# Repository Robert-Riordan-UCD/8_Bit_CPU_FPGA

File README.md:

# 8 Bit FPGA CPU

This is an 8-bit CPU design running on a Tang Nano 9k FPGA. The CPU design is based on [Ben Eaters Breadboard CPU](https://eater.net/8bit), which is based on the [Simple As Possible Computer](https://en.wikipedia.org/wiki/Simple-As-Possible_computer).

The CPU is made of 11 modules, which are designed in SystemVerilog and verified using [pyuvm](https://github.com/pyuvm/pyuvm).

This is a gif of the CPU calculating the fibonacci sequence and displaying it (in hexadecimal).

# Getting Started

This project is not fully complete yet and is currently only tested on my personal laptop and raspberry pi. However, this is the current process. (I am developing on Ubuntu 24 and used [this](https://www.geeklan.co.uk/?p=2919) guide to get up and running using an open source toolchain)

## Installation and Setup

The following programs are required:
1. ```yosys``` for synthisis.
2. ```nextpnr``` for place and route, and bitstream generation.
3. ```openFPGALoader``` for loading the bitstream.

```sudo apt insatll yosys nextpnr-gowin openfpgaloader```

Clone and navigate to the repository

```
git clone https://github.com/Robert-Riordan-UCD/8_Bit_CPU_FPGA
cd ./8_Bit_CPU_FPGA/
```

## Running

```make all upload```

## Testing

```pyuvm``` is required for testing.

```sudo apt install pyuvm```

To test each module navigate to the verif directory for that module and run make.

```
cd ./verif/<module>/
make
```

# Current Design Status

| Module                  | RTL | Verified | Runs on FPGA |
| :---------------------- | :-: | :-: | :-: |
| Clock                   |✅|✅|✅|
| Program Counter         |✅|✅|✅|
| A register              |✅|✅|✅|
| B Register              |✅|✅|✅|
| Memory Address Register |✅|✅|✅|
| Instruction Register    |✅|✅|✅|
| Random Access Memory    |✅|✅|✅|
| Arithmetic Logic Unit   |✅|✅|✅|
| Control                 |✅|✅|✅|
| Output                  |✅|✅|✅|
| Bus                     |✅|✅|✅|
| Bootloader              |✅|✅|✅|
||||
| Top                     |✅|❌|✅|

The output is currently in hexadecimal, because there was not enough LUTs on the Tang Nano 9k to implement a naive approach to decimal conversion using division. I will hopefully update this to a better approach soon.

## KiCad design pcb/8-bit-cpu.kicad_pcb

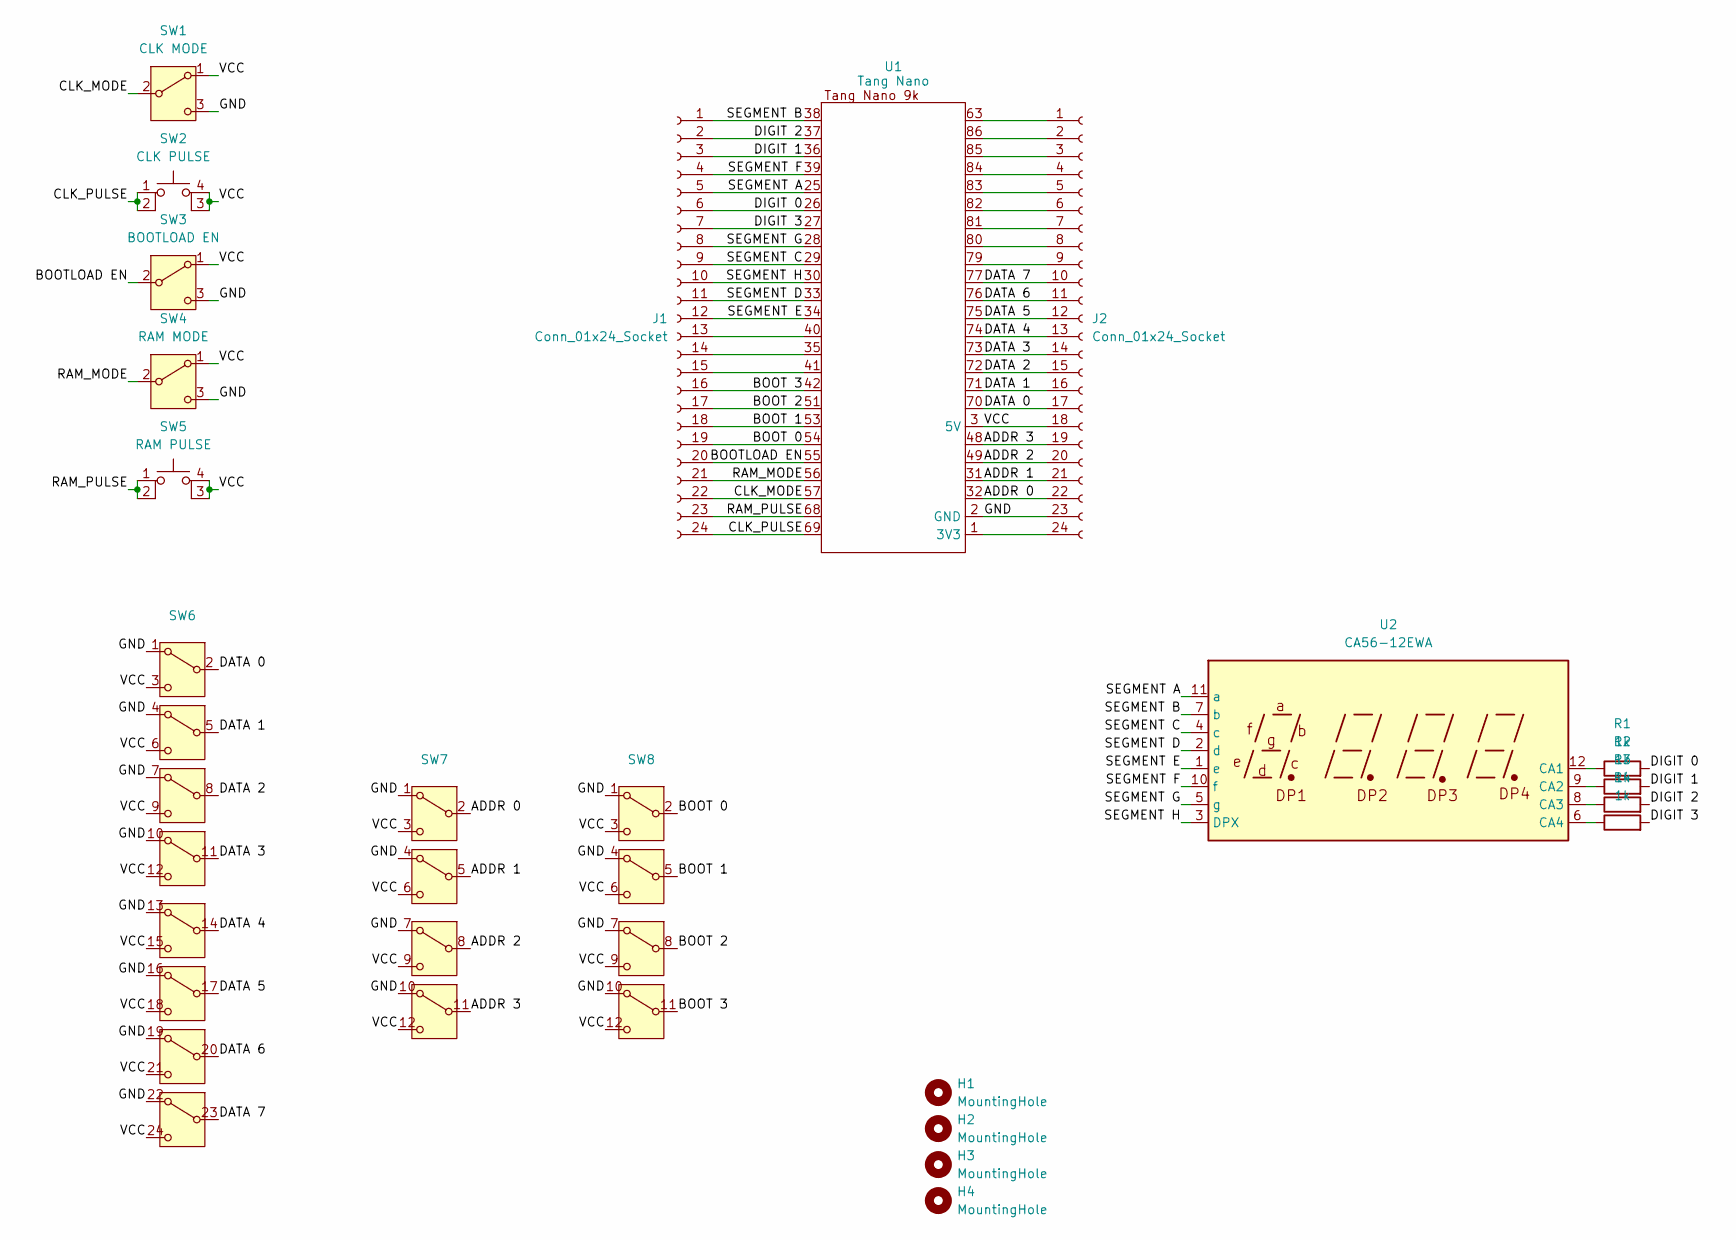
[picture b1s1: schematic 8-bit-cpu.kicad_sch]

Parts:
H1, H2, H3, H4: MountingHole; MountingHole_3.2mm_M3
J1, J2: Conn_01x24_Socket; PinHeader_1x24_P2.54mm_Vertical
R1, R2, R3, R4: 1k; R_Axial_DIN0309_L9.0mm_D3.2mm_P12.70mm_Horizontal
SW1: CLK MODE; DoubleThrowSwitch
SW2: CLK PULSE; tactile_switch
SW3: BOOTLOAD EN; DoubleThrowSwitch
SW4: RAM MODE; DoubleThrowSwitch
SW5: RAM PULSE; tactile_switch
SW6: 8xDoubleThrowSwitch
SW7, SW8: 4xDoubleThrowSwitch
U1: Tang Nano; TangNano
U2: CA56-12EWA

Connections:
/ADDR 0: J2.22, SW7.2, U1.32
/ADDR 1: J2.21, SW7.5, U1.31
/ADDR 2: J2.20, SW7.8, U1.49
/ADDR 3: J2.19, SW7.11, U1.48
/BOOT 0: J1.19, SW8.2, U1.54
/BOOT 1: J1.18, SW8.5, U1.53
/BOOT 2: J1.17, SW8.8, U1.51
/BOOT 3: J1.16, SW8.11, U1.42
/BOOTLOAD EN: J1.20, SW3.2 (B), U1.55
/CLK_MODE: J1.22, SW1.2 (B), U1.57
/CLK_PULSE: J1.24, SW2.1, SW2.2, U1.69
/DATA 0: J2.17, SW6.2, U1.70
/DATA 1: J2.16, SW6.5, U1.71
/DATA 2: J2.15, SW6.8, U1.72
/DATA 3: J2.14, SW6.11, U1.73
/DATA 4: J2.13, SW6.14, U1.74
/DATA 5: J2.12, SW6.17, U1.75
/DATA 6: J2.11, SW6.20, U1.76
/DATA 7: J2.10, SW6.23, U1.77
/DIGIT 0: J1.6, R1.2, U1.26
/DIGIT 1: J1.3, R2.2, U1.36
/DIGIT 2: J1.2, R3.2, U1.37
/DIGIT 3: J1.7, R4.2, U1.27
/GND: J2.23, SW1.3 (C), SW3.3 (C), SW4.3 (C), SW6.1, SW6.4, SW6.7, SW6.10, SW6.13, SW6.16, SW6.19, SW6.22, SW7.1, SW7.4, SW7.7, SW7.10, SW8.1, SW8.4, SW8.7, SW8.10, U1.2 (GND)
/RAM_MODE: J1.21, SW4.2 (B), U1.56
/RAM_PULSE: J1.23, SW5.1, SW5.2, U1.68
/SEGMENT A: J1.5, U1.25, U2.11 (a)
/SEGMENT B: J1.1, U1.38, U2.7 (b)
/SEGMENT C: J1.9, U1.29, U2.4 (c)
/SEGMENT D: J1.11, U1.33, U2.2 (d)
/SEGMENT E: J1.12, U1.34, U2.1 (e)
/SEGMENT F: J1.4, U1.39, U2.10 (f)
/SEGMENT G: J1.8, U1.28, U2.5 (g)
/SEGMENT H: J1.10, U1.30, U2.3 (DPX)
/VCC: J2.18, SW1.1 (A), SW2.3 (K), SW2.4 (A), SW3.1 (A), SW4.1 (A), SW5.3 (K), SW5.4 (A), SW6.3, SW6.6, SW6.9, SW6.12, SW6.15, SW6.18, SW6.21, SW6.24, SW7.3, SW7.6, SW7.9, SW7.12, SW8.3, SW8.6, SW8.9, SW8.12, U1.3 (5V)
unnamed: J1.13, U1.40
unnamed: J1.14, U1.35
unnamed: J1.15, U1.41
unnamed: J2.1, U1.63
unnamed: J2.2, U1.86
unnamed: J2.3, U1.85
unnamed: J2.4, U1.84
unnamed: J2.5, U1.83
unnamed: J2.6, U1.82
unnamed: J2.7, U1.81
unnamed: J2.8, U1.80
unnamed: J2.9, U1.79
unnamed: J2.24, U1.1 (3V3)
unnamed: R1.1, U2.12 (CA1)
unnamed: R2.1, U2.9 (CA2)
unnamed: R3.1, U2.8 (CA3)
unnamed: R4.1, U2.6 (CA4)

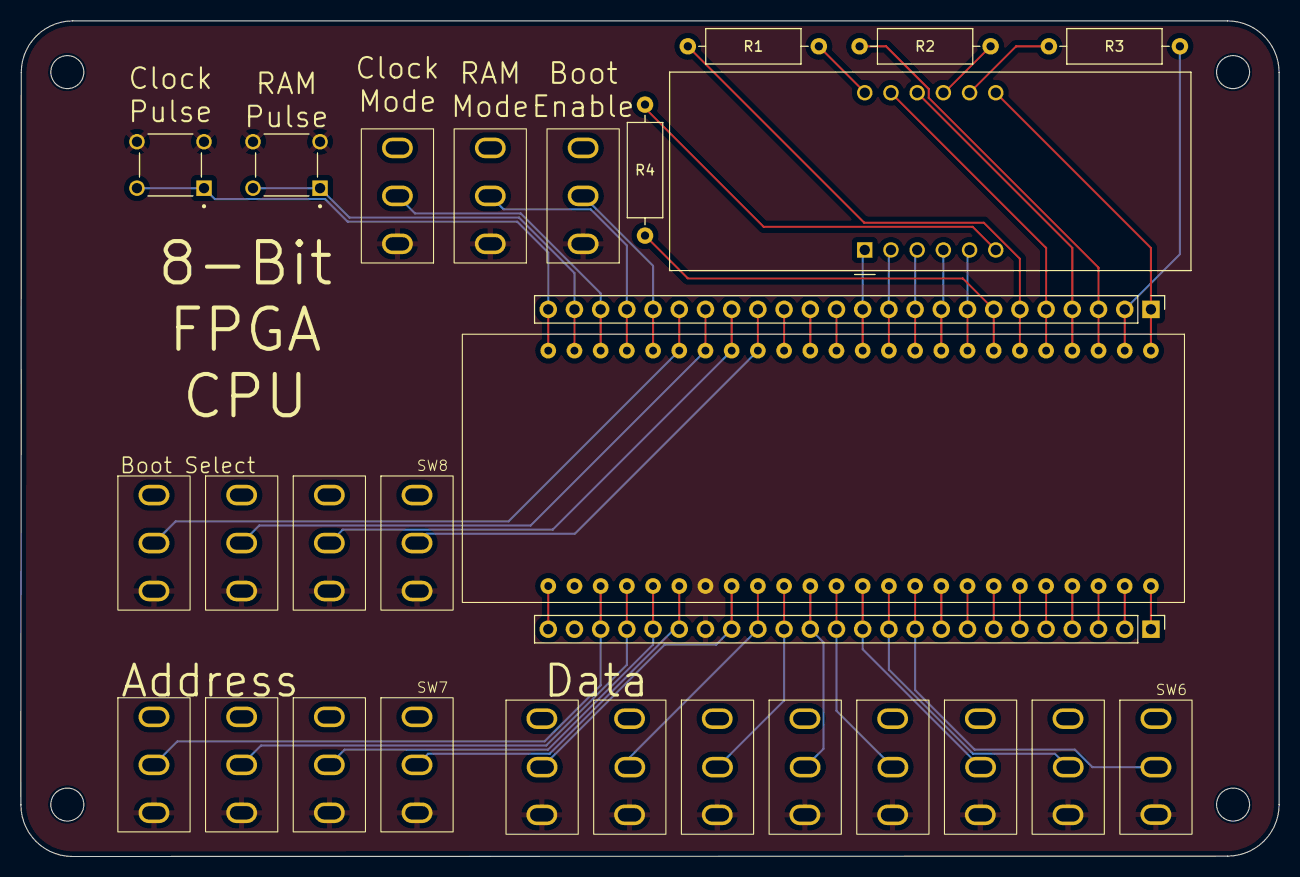
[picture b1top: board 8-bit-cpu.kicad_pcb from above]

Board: 2 copper layers, 122.0 x 81.0 mm, 20 parts (0 on the bottom side), 52 nets.

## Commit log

2025-06-17 Initial commit. Clock running on tang nano with continious and manual mode
2025-07-01 Shortened simulation wait time
2025-07-01 Added a method to send the bitstream to my rpi over ssh instead of using a USB stick
2025-07-01 Added PC, hooked up PC in top, and updated constraints
2025-07-01 Can build remotely on my rpi now
2025-07-01 Clock mode and pulse are now connected to GPIO
2025-07-05 Inital UVM testbench setup. Testbench works but not running random tests or full coverage
2025-07-05 Removed accidentaly added file
2025-07-05 Added random testing. Cleaned code and fixed bugs
2025-07-05 Added verif outputs to make clean
2025-07-06 Fixed error in testbench. Updating expected value to early.
2025-07-06 Removed old testbench
2025-07-06 Created PC dir in verif
2025-07-09 Register RTL added
2025-07-10 Added ALU and verification setup
2025-07-10 Fixed coverage for ALU and added reset
2025-07-10 Removed unused import
2025-07-10 Moved sequences from test to own file
2025-07-10 Added coverage sequences for ALU. ALU full verified now
2025-07-11 Initial register testing and coverage
2025-07-13 Register scoreboard running correctly
2025-07-13 Added edge case and operation sequences
2025-07-13 A/B register verification complete
2025-07-14 Added bus mask to register for instruction register
2025-07-14 Updated status
2025-07-14 Added instruction register testing
2025-07-14 Added MAR
2025-07-15 MAR verified
2025-07-15 Added all current modules to top
2025-07-15 Fixed directory name
2025-07-15 Fixed ALU scoreboard
2025-07-15 Created RAM
2025-07-19 RAM verified
2025-07-19 PC verified properly
2025-07-19 Control interface and micorcode coutner setup
2025-07-19 Control verif setup. Fetch cycle visually working
2025-07-19 Control RTL complete
2025-07-19 Added all test sequeces
2025-07-19 Removed old file
2025-07-19 Updated top with control
2025-07-19 Added halt signal to clock
2025-07-20 Control scoreboard setup
2025-07-20 Added ADD sequence and fixed bug in ADD RTL
2025-07-20 Added store A and SUB sequences. Fixed bug in SUB RTL
2025-07-20 Added all remaing non-conditional instruction sequences
2025-07-20 Added jump conditional RTL and sequences
2025-07-20 Added random instruction sequences
2025-07-20 Instruction coverage added
2025-07-20 Added control output signals coverage
2025-07-20 Coverage added for ALU carry and zero. Control verified
2025-07-23 Created display RTL and setup verification
2025-07-23 Figured out how much GPIO I will need
2025-07-23 Scoreboard working
2025-07-23 Added coverage and updated sequences< Display verified
2025-07-23 Fixed typo
2025-07-24 Clock verified
2025-07-25 Changed functions to tasks for yosys
2025-07-26 Added reset to control sensitivity list. Made task automatic to make icarus happy
2025-07-26 Moved top to ./src and started verification
2025-07-26 Fixed old signal names
2025-07-26 yosys complained about signal from sensitivity list and other signals being used together so I have to seperate them
2025-08-01 Yosys can't generate tristate bus logic. Created a new bus module. Will have to update all modules to work without tristate logic
2025-08-14 Clock running on FPGA
2025-08-14 Switched PC to seperate input and output buses. PC running on FPGA
2025-08-14 Switched register to seperate input and output buses. I reg running on FPGA
2025-08-14 Bus module working on FPGA
2025-08-14 Control working on the FPGA
2025-08-14 Removed debug IO
2025-08-14 MAR running on FPGA
2025-08-15 RAM running on FPGA
2025-08-15 A/B registers running on FPGA. Added missing ram_bus_out wire
2025-08-15 ALU working on FPGA
2025-08-15 Display working on FPGA! All modules are working together and programs are running!
2025-08-15 Added fibinacci program
2025-08-15 Added multiply program!
2025-08-17 PC tests updated and passing for new bus architecture
2025-08-17 A/B register tests updated and passing for new bus architecture
2025-08-17 I register tests updated and passing for new bus architecture
2025-08-17 RAM tests updated and passing for new bus architecture
2025-08-17 ALU tests updated and passing for new bus architecture
2025-08-18 Update README.md with general info and how to run
2025-08-18 Updated Makefile to allow local bitsteam upload
2025-08-18 Removed unnecessary pwd
2025-08-18 Fixed indentation error
2025-08-18 Added a gif of the FPGA running
2025-08-18 Added gif of fibonacci sequence to the read me
2025-08-18 Display tests updated and passing for new bus architecture
2025-08-18 Fixed error in display. Using old variable name
2025-08-19 Created a bootloader. Updated control with new bootloader signals
2025-08-19 Updated bootloader coverage
2025-08-19 Updated bootloader scoreboard and fixed errors in bootloader
2025-09-04 Updated clock coverage to use cocotb CoverPoint and CoverCross
2025-09-04 Updated control coverage to use cocotb CoverPoint, CoverCross, CoverCheck
2025-09-04 Updated display coverage to use cocotb CoverPoint
2025-09-04 Updated instruction reg coverage to use cocotb CoverPoint
2025-09-04 Updated MAR coverage to use cocotb CoverPoint
2025-09-04 Updated PC coverage to use cocotb CoverPoint
2025-09-04 Updated RAM coverage to use cocotb CoverPoint
2025-09-04 Updated register coverage to use cocotb CoverPoint
2025-09-05 Updated bootloader coverage to use cocotb CoverPoint and CoverCross
2025-09-05 Updated ALU coverage to use cocotb CoverPoint and CoverCross
2025-09-05 Fixed path to bitstream
2025-09-10 Bootloader fully integrated and full CPU workin on FPGA now
2025-09-10 Added toggle and multiply programs to bootloader
2025-09-10 Top verif updated. Can only be used for checking waves. It does no verification
2025-09-11 Updated Makefile to avoid using Makefile on rpi. And added permenanty flash option.
2025-09-11 Reset can be trigger even when the clock is halted now
2025-09-11 Programming mode decoupled from clock
2025-09-11 Fixed cont_addr getting program switches and removed unused signal
2025-09-11 PCB design
2025-09-11 Updated top with MAR IO changes
2025-09-11 Added current limiting resistors to display
2025-09-24 Moved boot select switch to clear HDMI port
2025-09-24 Reverse bit ordering to match PCB
2025-09-24 Switched to new 7 segment display with reverse polarity. Switched RAM pulse polarity to because it is using the onboard button now
2025-09-24 Shortened microcode counter
2025-09-25 Spelling
2025-09-25 Removed unneeded instructions
